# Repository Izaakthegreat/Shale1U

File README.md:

# Shale1U
A little 1U DIY Eurorack Utility amp.

Shale is stereo line in and dual passive attenuator module. It's 20hp and Intellijel 1U, though I may add slots to make it PulpLogic compatible.

Artwork is done by @brilli.antoinette on instagram.

Build guide coming soon!

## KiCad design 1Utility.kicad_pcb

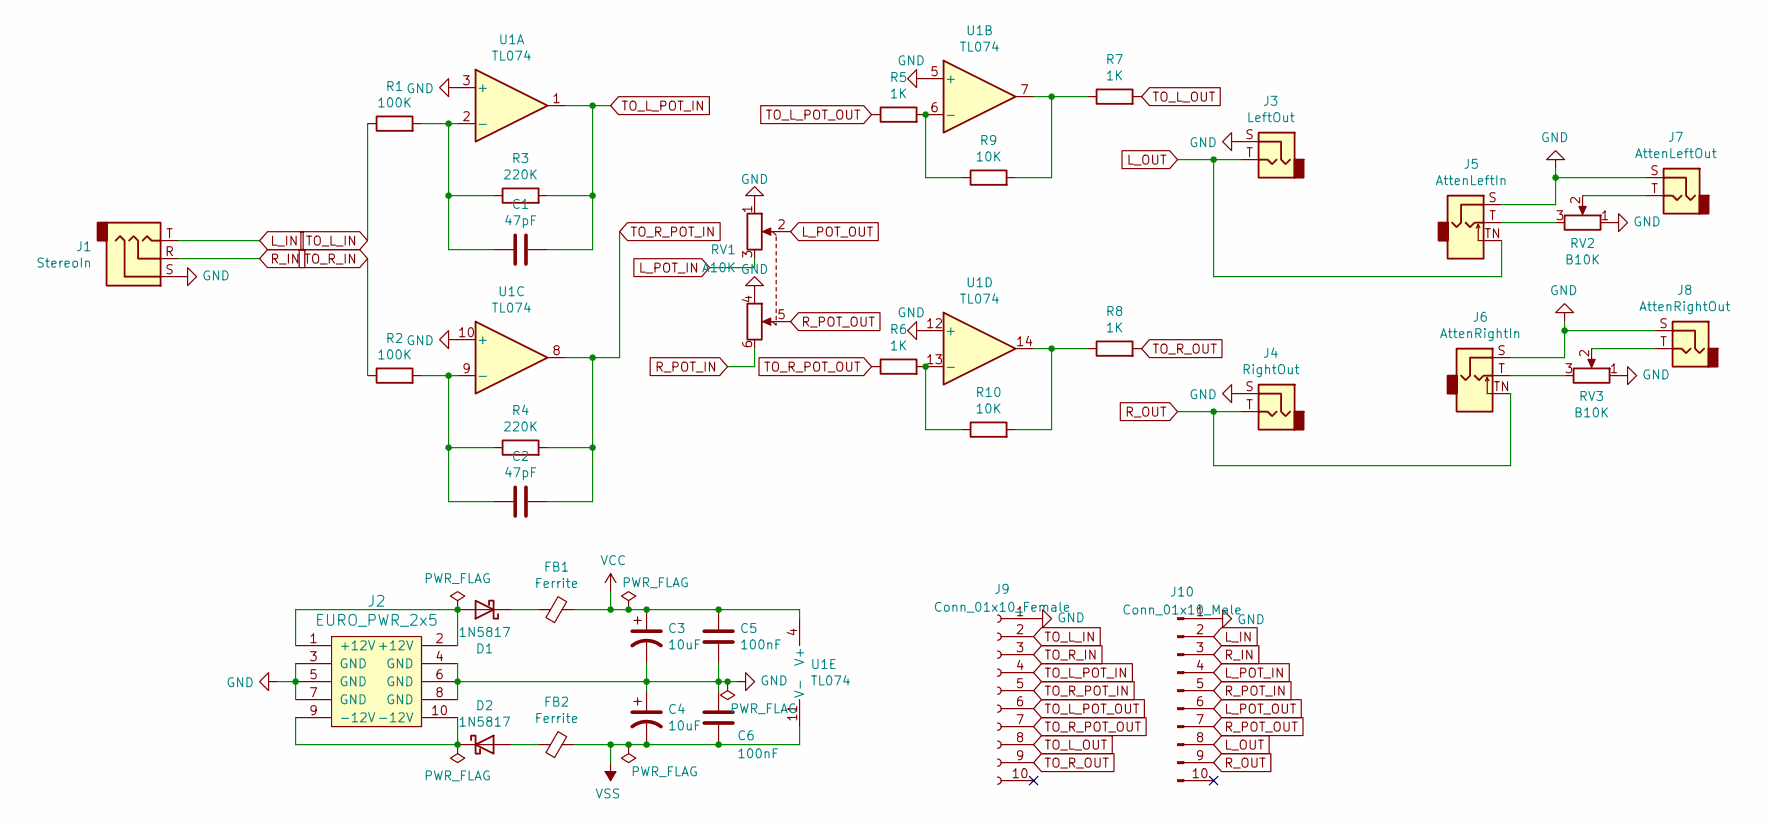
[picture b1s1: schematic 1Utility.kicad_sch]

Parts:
C1, C2: 47pF; C_Disc_D7.0mm_W2.5mm_P5.00mm
C3, C4: 10uF; CP_Radial_D4.0mm_P2.00mm
C5, C6: 100nF; C_Disc_D7.0mm_W2.5mm_P5.00mm
D1, D2: 1N5817; D_DO-41_SOD81_P7.62mm_Horizontal
FB1, FB2: Ferrite; R_Axial_DIN0207_L6.3mm_D2.5mm_P10.16mm_Horizontal
J1: StereoIn; WQP-WQP518MA
J2: EURO_PWR_2x5; Eurorack_Power
J3: LeftOut; WQP-WQP518MA
J4: RightOut; WQP-WQP518MA
J5: AttenLeftIn; WQP-WQP518MA
J6: AttenRightIn; WQP-WQP518MA
J7: AttenLeftOut; WQP-WQP518MA
J8: AttenRightOut; WQP-WQP518MA
J9: Conn_01x10_Female; PinSocket_1x10_P2.54mm_Vertical
J10: Conn_01x10_Male; PinHeader_1x10_P2.54mm_Vertical
R1, R2: 100K; R_Axial_DIN0207_L6.3mm_D2.5mm_P10.16mm_Horizontal
R3, R4: 220K; R_Axial_DIN0207_L6.3mm_D2.5mm_P10.16mm_Horizontal
R5, R6, R7, R8: 1K; R_Axial_DIN0207_L6.3mm_D2.5mm_P10.16mm_Horizontal
R9, R10: 10K; R_Axial_DIN0207_L6.3mm_D2.5mm_P10.16mm_Horizontal
RV1: A10K; Potentiometer_Alpha_RD902F-40-00D_Dual_Vertical
RV2, RV3: B10K; Potentiometer_Alpha_RD901F-40-00D_Single_Vertical
U1: TL074; DIP-14_W7.62mm_Socket_LongPads

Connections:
GND: C3.2, C4.1, C5.1, C6.2, J1.S, J2.3 (GND), J2.4 (GND), J2.5 (GND), J2.6 (GND), J2.7 (GND), J2.8 (GND), J3.S, J4.S, J5.S, J6.S, J7.S, J8.S, J9.1, J10.1, RV1.1, RV1.4, RV2.1, RV3.1, U1.3 (+), U1.5 (+), U1.10 (+), U1.12 (+)
L_IN: J1.T, J10.2
L_OUT: J3.T, J5.TN, J10.8
L_POT_IN: J10.4, RV1.3
L_POT_OUT: J10.6, RV1.2
unnamed: C1.2, R1.2, R3.1, U1.2 (-)
unnamed: C2.2, R2.2, R4.1, U1.9 (-)
unnamed: D1.1 (K), FB1.1
unnamed: D1.2 (A), J2.1 (+12V), J2.2 (+12V)
unnamed: D2.1 (K), J2.9 (-12V), J2.10 (-12V)
unnamed: D2.2 (A), FB2.1
unnamed: J5.T, RV2.3
unnamed: J6.T, RV3.3
unnamed: J7.T, RV2.2
unnamed: J8.T, RV3.2
unnamed: R5.2, R9.1, U1.6 (-)
unnamed: R6.2, R10.1, U1.13 (-)
unnamed: R8.1, R10.2, U1.14
unnamed: R7.1, R9.2, U1.7
R_IN: J1.R, J10.3
R_OUT: J4.T, J6.TN, J10.9
R_POT_IN: J10.5, RV1.6
R_POT_OUT: J10.7, RV1.5
TO_L_IN: J9.2, R1.1
TO_L_OUT: J9.8, R7.2
TO_L_POT_IN: C1.1, J9.4, R3.2, U1.1
TO_L_POT_OUT: J9.6, R5.1
TO_R_IN: J9.3, R2.1
TO_R_OUT: J9.9, R8.2
TO_R_POT_IN: C2.1, J9.5, R4.2, U1.8
TO_R_POT_OUT: J9.7, R6.1
VCC: C3.1, C5.2, FB1.2, U1.4 (V+)
VSS: C4.2, C6.1, FB2.2, U1.11 (V-)

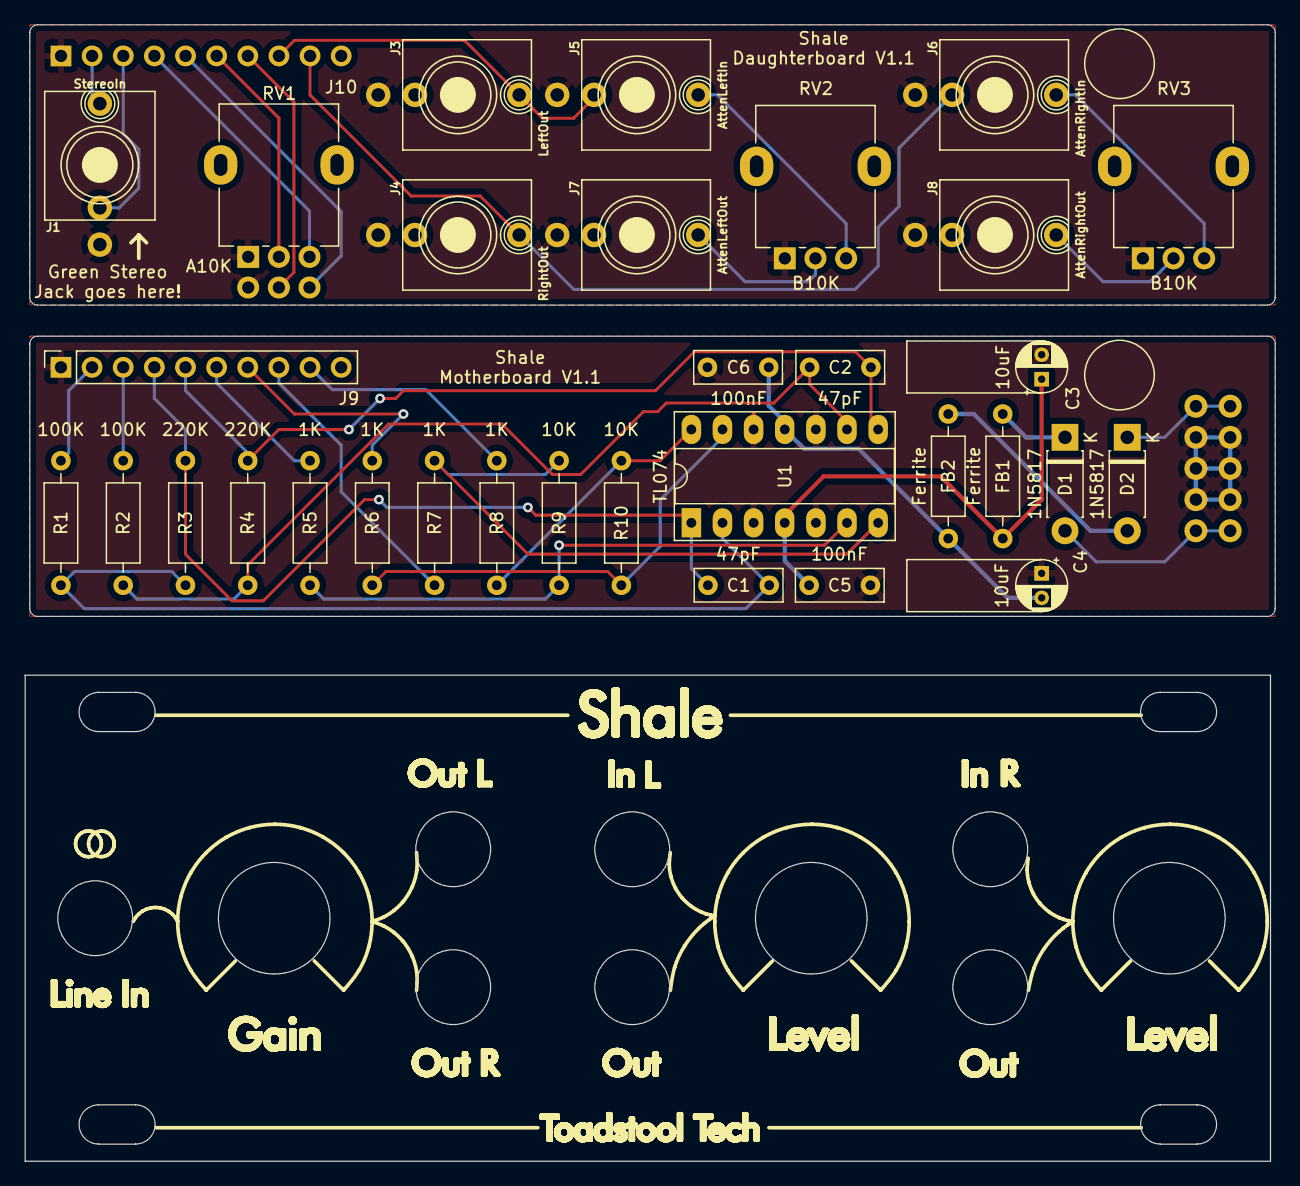
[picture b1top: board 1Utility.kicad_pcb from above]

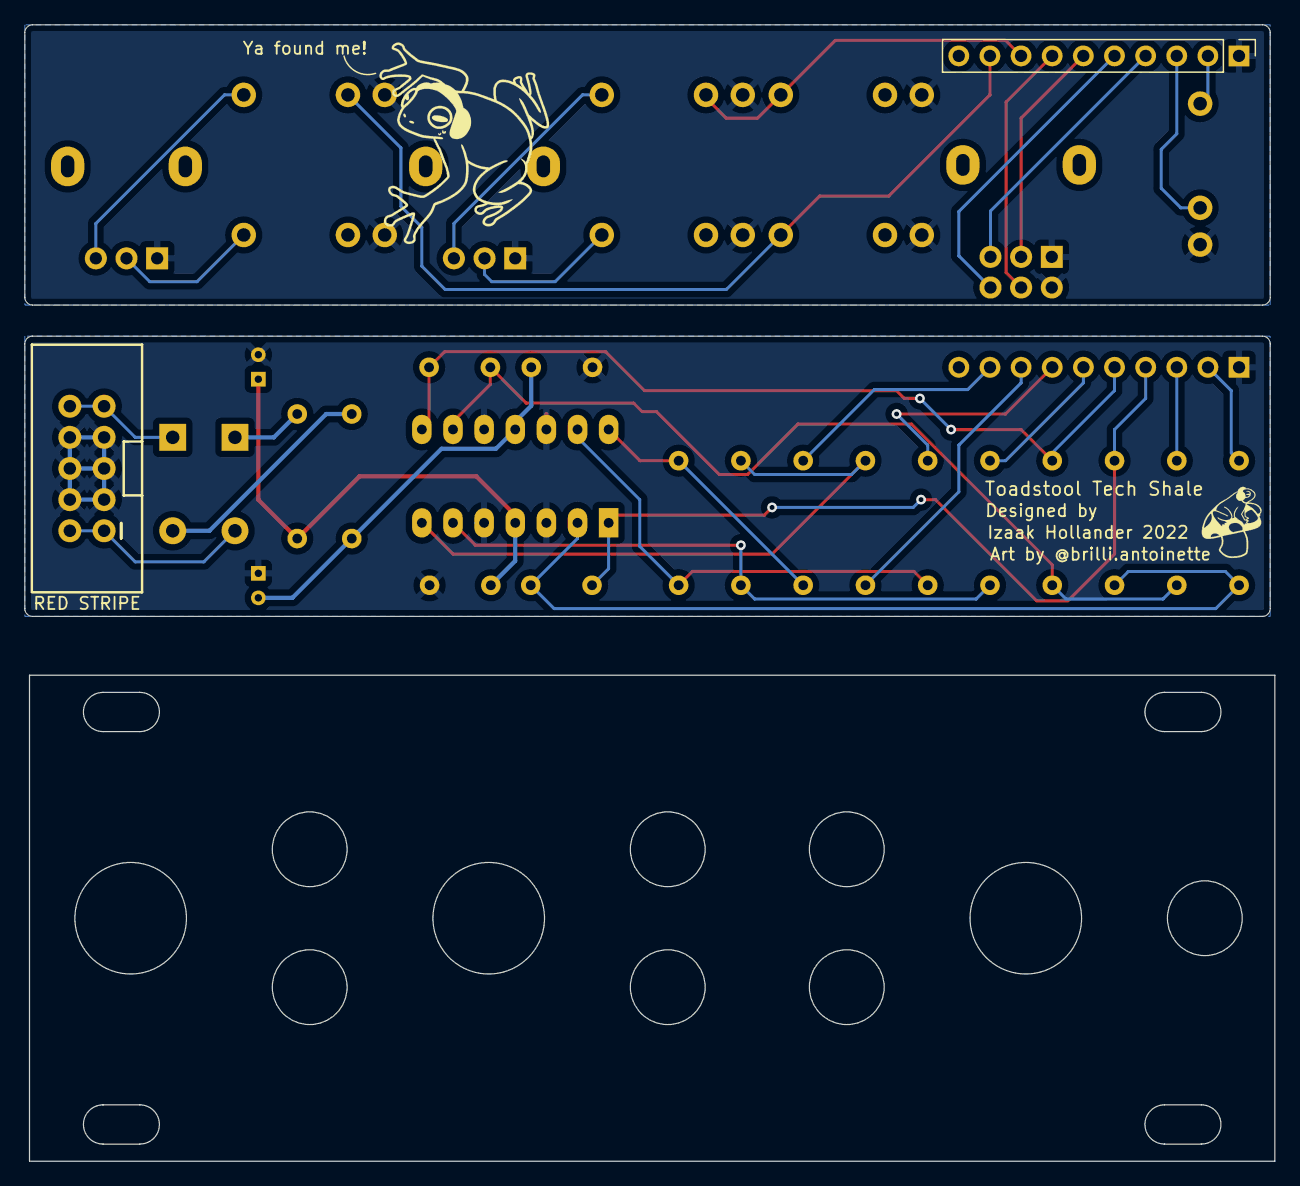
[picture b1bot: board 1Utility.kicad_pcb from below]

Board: 2 copper layers, 102.0 x 92.7 mm, 34 parts (2 on the bottom side), 32 nets.

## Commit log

2022-02-24 added v1.1 panel, schematic and pcb
